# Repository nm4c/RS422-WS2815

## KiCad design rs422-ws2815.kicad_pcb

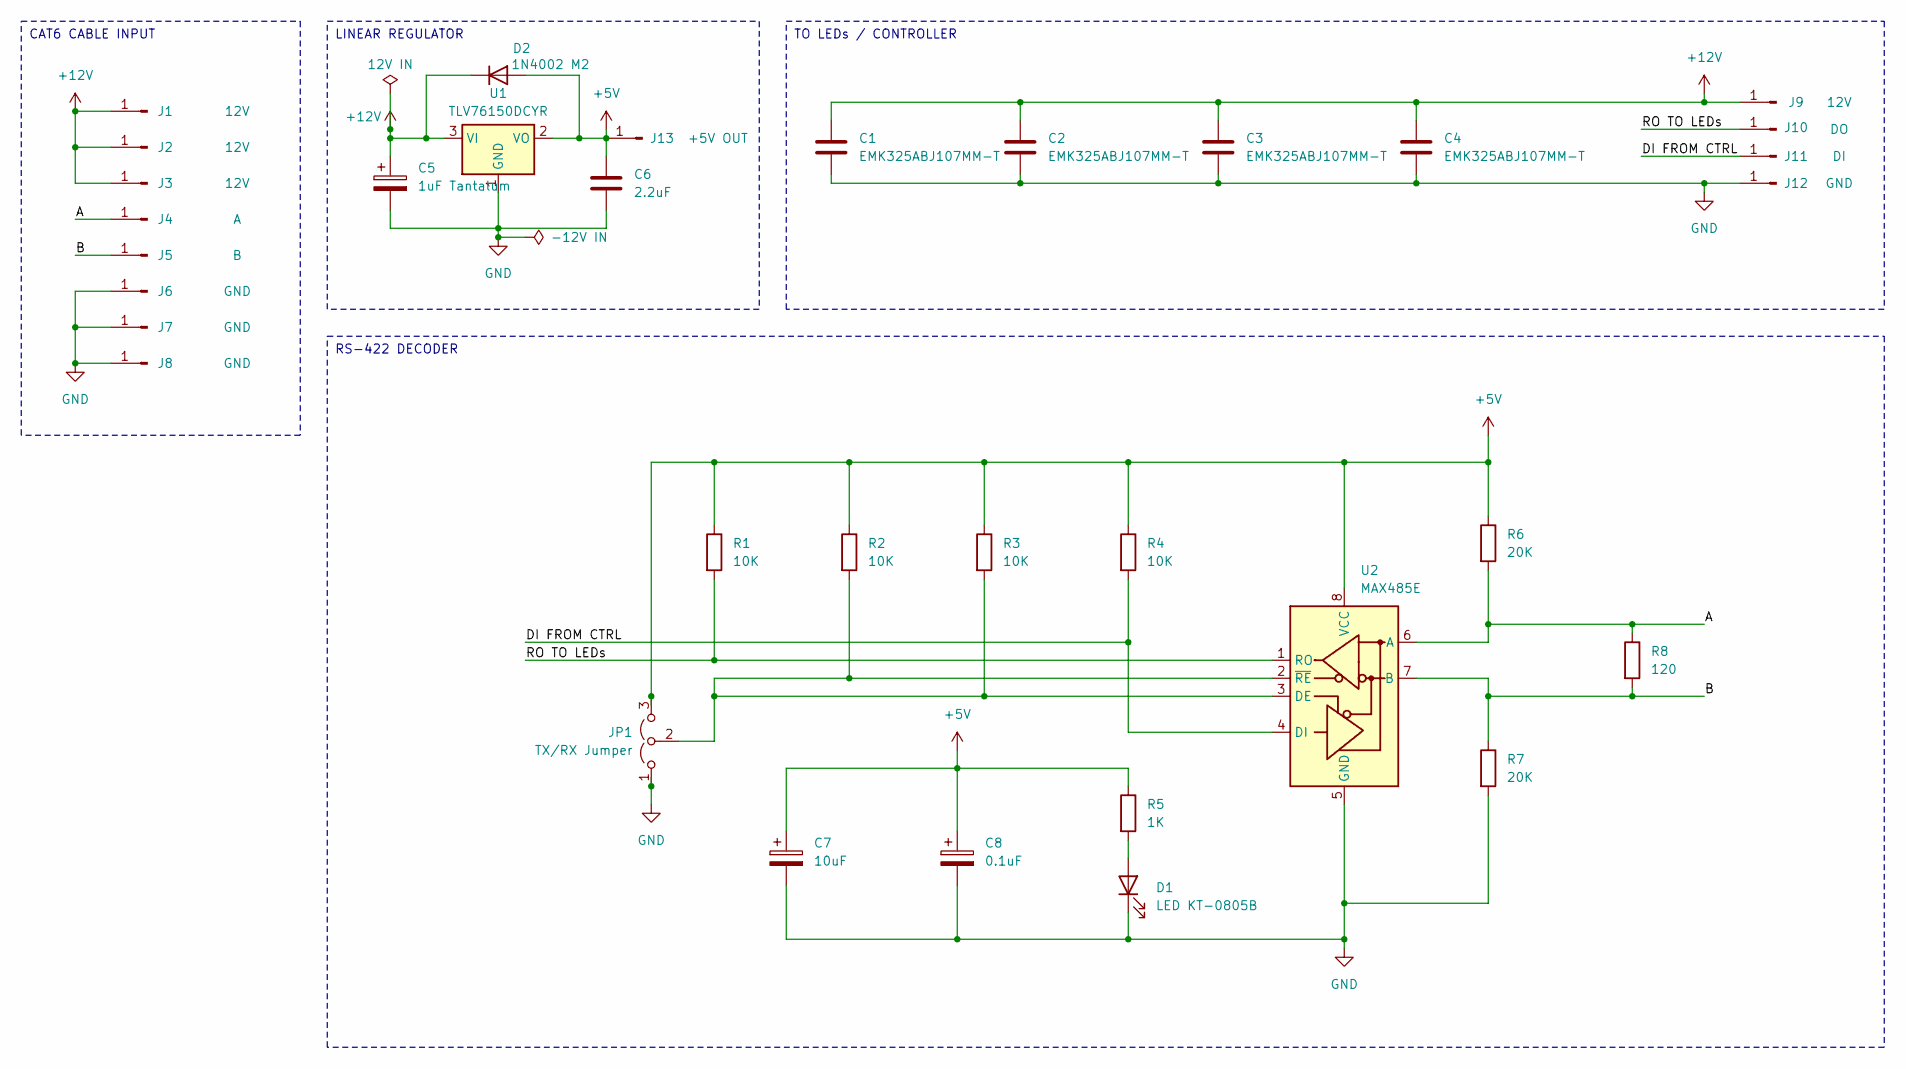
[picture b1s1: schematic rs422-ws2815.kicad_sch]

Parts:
C1, C2, C3, C4: EMK325ABJ107MM-T; C_1210_3225Metric
C5: 1uF Tantalum; C_0805_2012Metric
C6: 2.2uF; C_0805_2012Metric
C7: 10uF; C_0805_2012Metric
C8: 0.1uF; C_0603_1608Metric
D1: LED KT-0805B; LED_0805_2012Metric
D2: 1N4002 M2; D_SMA
J1, J2, J3, J9: 12V; SolderWire-0.5sqmm_1x01_D0.9mm_OD2.1mm
J4: A; SolderWire-0.5sqmm_1x01_D0.9mm_OD2.1mm
J5: B; SolderWire-0.5sqmm_1x01_D0.9mm_OD2.1mm
J6, J7, J8, J12: GND; SolderWire-0.5sqmm_1x01_D0.9mm_OD2.1mm
J10: DO; SolderWire-0.5sqmm_1x01_D0.9mm_OD2.1mm
J11: DI; SolderWire-0.5sqmm_1x01_D0.9mm_OD2.1mm
J13: +5V OUT; SolderWire-0.5sqmm_1x01_D0.9mm_OD2.1mm
JP1: TX/RX Jumper; SolderJumper-3_P2.0mm_Open_TrianglePad1.0x1.5mm
R1, R2, R3, R4: 10K; R_0603_1608Metric
R5: 1K; R_0603_1608Metric
R6, R7: 20K; R_0603_1608Metric
R8: 120; R_0603_1608Metric
U1: TLV76150DCYR; SOT-223-3_TabPin2
U2: MAX485E; SOIC-8_3.9x4.9mm_P1.27mm

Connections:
+5V: C6.1, C7.1, C8.1, D2.2 (A), J13.1, JP1.3 (B), R1.1, R2.1, R3.1, R4.1, R5.1, R6.1, U1.2 (VO), U2.8 (VCC)
+12V: C1.1, C2.1, C3.1, C4.1, C5.1, D2.1 (K), J1.1, J2.1, J3.1, J9.1, U1.3 (VI)
/A: J4.1, R6.2, R8.1, U2.6 (A)
/B: J5.1, R7.1, R8.2, U2.7 (B)
/DI FROM CTRL: J11.1, R4.2, U2.4 (DI)
/RO TO LEDs: J10.1, R1.2, U2.1 (RO)
GND: C1.2, C2.2, C3.2, C4.2, C5.2, C6.2, C7.2, C8.2, D1.1 (K), J6.1, J7.1, J8.1, J12.1, JP1.1 (A), R7.2, U1.1 (GND), U2.5 (GND)
unnamed: D1.2 (A), R5.2
unnamed: JP1.2 (C), R2.2, R3.2, U2.2 (~RE), U2.3 (DE)

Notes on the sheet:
LINEAR REGULATOR
RS-422 DECODER
CAT6 CABLE INPUT
TO LEDs / CONTROLLER

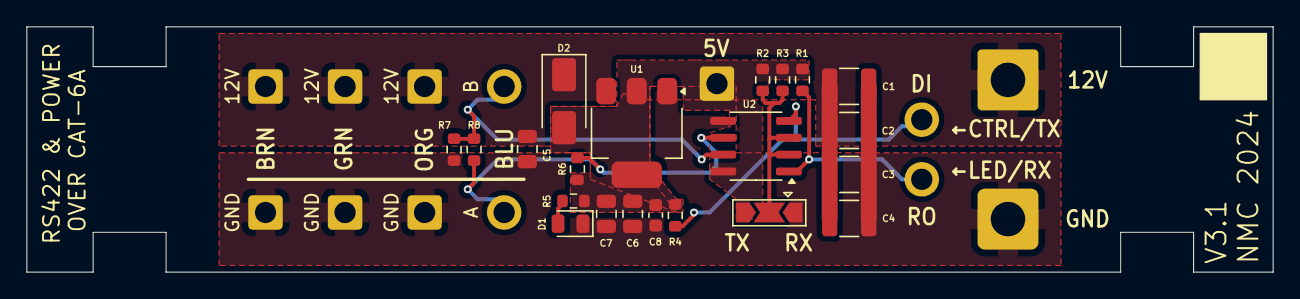
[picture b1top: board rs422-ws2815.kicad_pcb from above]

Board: 2 copper layers, 94.0 x 18.5 mm, 34 parts (0 on the bottom side), 9 nets.

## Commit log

2024-11-26 Add files via upload
    Changed to TI TLV761 5V reg & updated caps to suit
